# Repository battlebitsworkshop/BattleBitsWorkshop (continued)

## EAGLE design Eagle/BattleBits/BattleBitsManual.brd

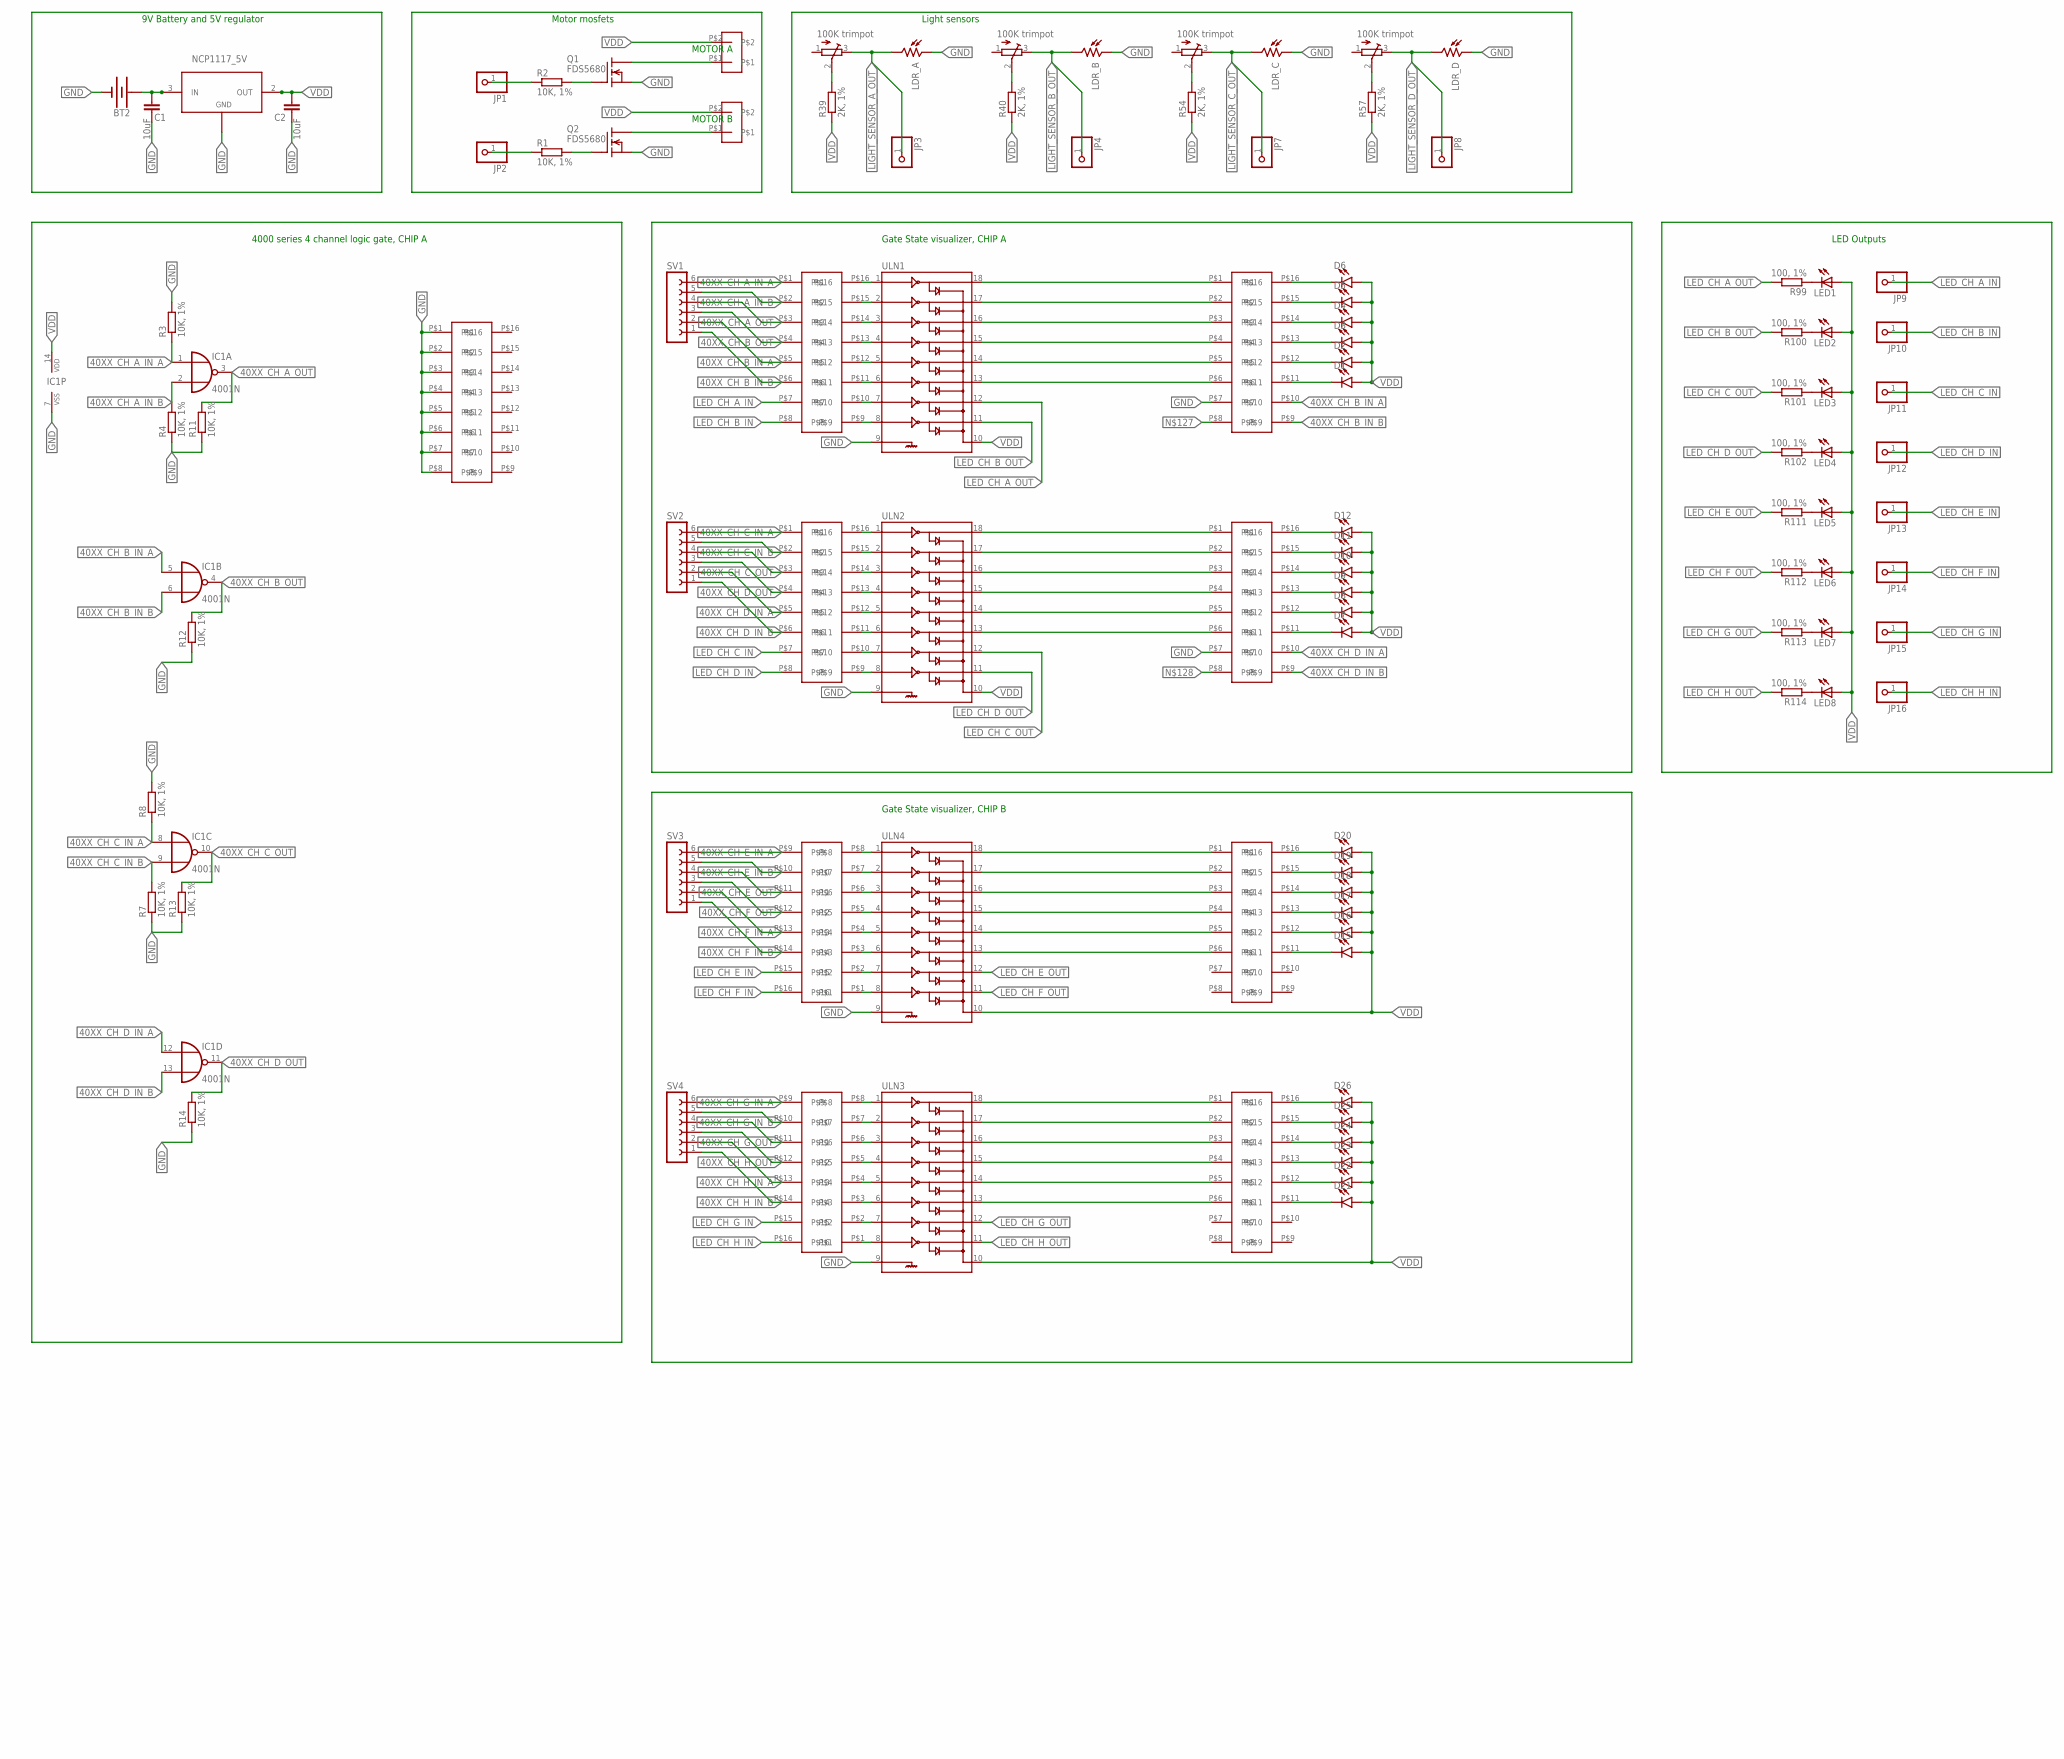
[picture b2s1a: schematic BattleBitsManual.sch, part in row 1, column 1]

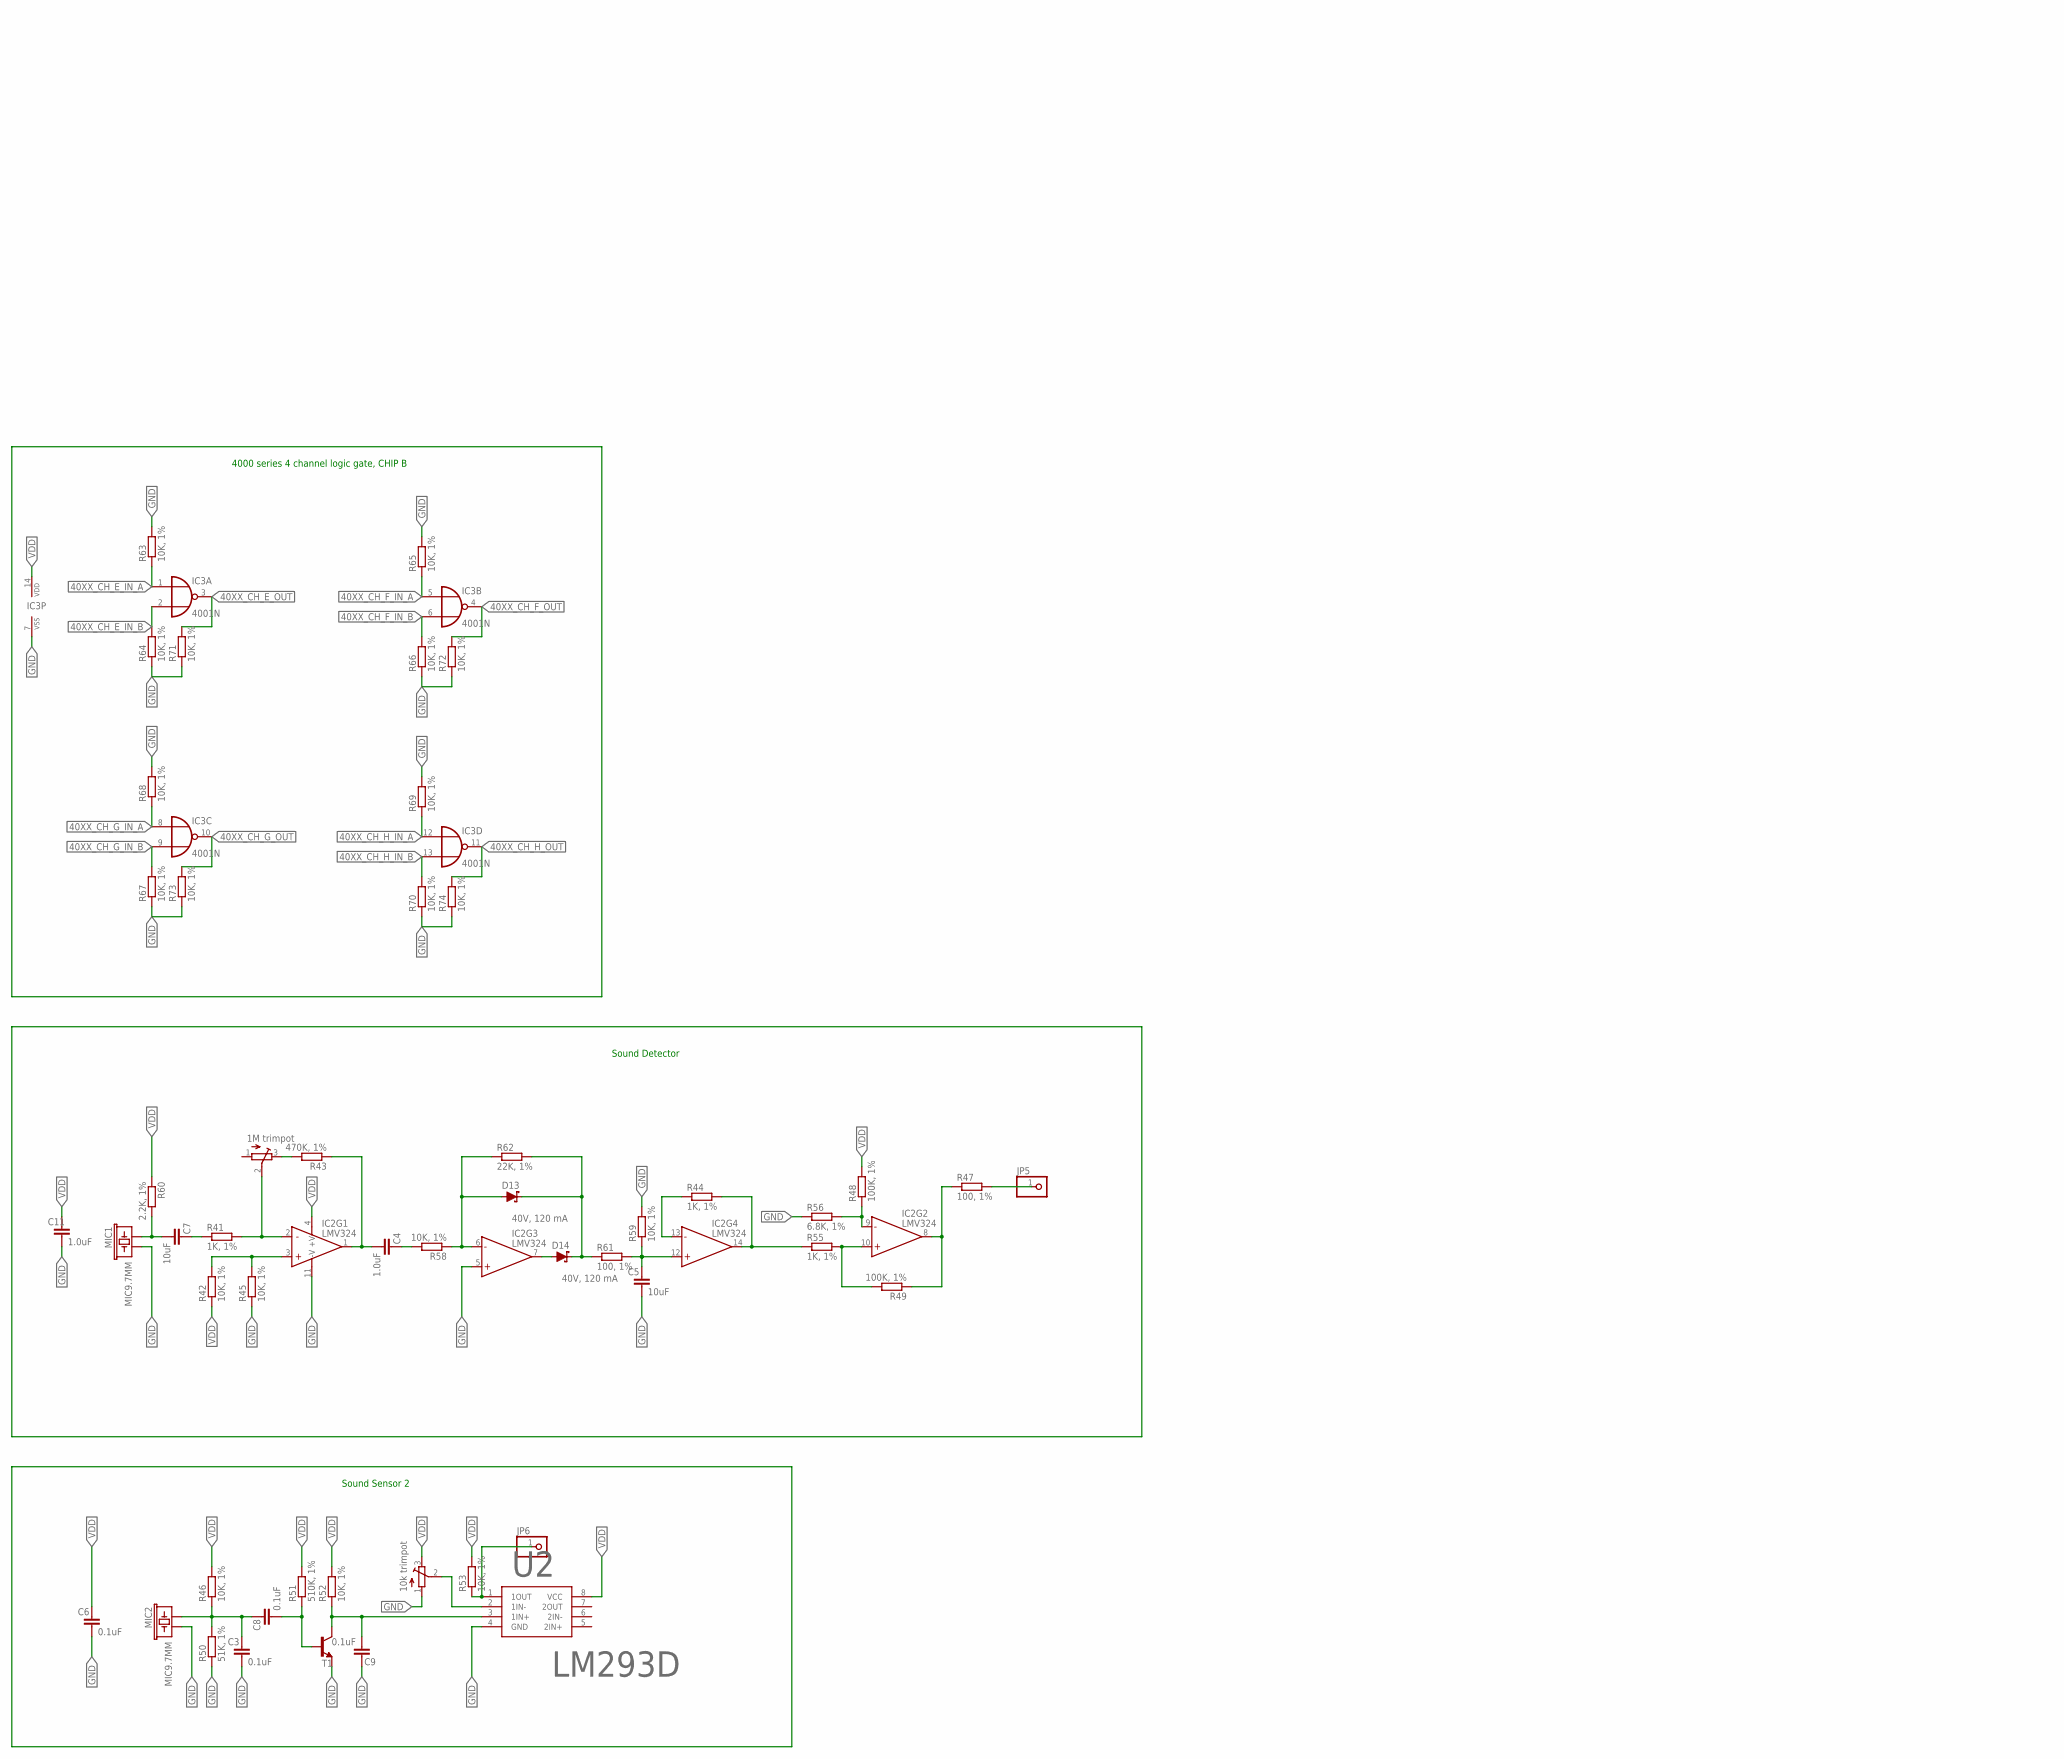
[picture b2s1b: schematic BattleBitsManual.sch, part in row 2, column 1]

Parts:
BT2: BATTERY-9V; BATTCON_9V
C1, C2, C5, C7: 10uF; C3216
C3, C6, C8, C9: 0.1uF; C3216
C4, C11: 1.0uF; C3216
D1, D2, D3, D4, D5, D6, D7, D8, D9, D10, D11, D12, D15, D16, D17, D18, D19, D20, D21, D22, D23, D24, D25, D26: LED1206; LED-1206
D13, D14: 40V, 120 mA; SOT23-3
IC1, IC3: 4001N; DIL14
IC2: LMV324; SO014
JP1, JP2, JP3, JP4, JP5, JP6, JP7, JP8, JP9, JP10, JP11, JP12, JP13, JP14, JP15, JP16: PINHD-1X1; 1X01
LDR_A: V1060_21; TO-5_V10
LDR_B: V1060_21; TO-5_V10
LDR_C: V1060_21; TO-5_V10
LDR_D: V1060_21; TO-5_V10
LED1, LED2, LED3, LED4, LED5, LED6, LED7, LED8: LED5MM
MIC1, MIC2: MIC9.7MM; MIC-9.7MM
Q1, Q2: FDS5680; SO-8
R1, R2, R3, R4, R7, R8, R11, R12, R13, R14, R42, R45, R46, R52, R53, R58, R59, R63, R64, R65, R66, R67, R68, R69, R70, R71, R72, R73, R74: 10K, 1%; R3216
R39, R40, R54, R57: 2K, 1%; R3216
R41, R44, R55: 1K, 1%; R3216
R43: 470K, 1%; R3216
R47, R61, R99, R100, R101, R102, R111, R112, R113, R114: 100, 1%; R3216
R48, R49: 100K, 1%; R3216
R50: 51K, 1%; R3216
R51: 510K, 1%; R3216
R56: 6.8K, 1%; R3216
R60: 2.2K, 1%; R3216
R62: 22K, 1%; R3216
SV1, SV2, SV3, SV4: FE06-1; FE06
T1: BC808-NPN-SOT23-BEC; SOT23-BEC
TM1, TM2, TM5, TM6: 100K trimpot; TC33X
TM3: 1M trimpot; TC33X
TM4: 10k trimpot; TC33X
U1: NCP1117_5V; SOT-223
U2: LM293D; 8-SOIC
U$1, U$2: MOTOR; GEARMOTOR
U$3, U$4, U$5, U$6, U$7, U$8, U$9, U$10, U$11: 8_RES_ISO_SOIC16
ULN1, ULN2, ULN3, ULN4: ULN2803SOICW; SO18L

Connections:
40XX_CH_A_IN_A: IC1.1 (I0), R3.1, SV1.6, U$9.P$1
40XX_CH_A_IN_B: IC1.2 (I1), R4.2, SV1.5, U$9.P$2
40XX_CH_A_OUT: IC1.3 (O), R11.2, SV1.4, U$9.P$3
40XX_CH_B_IN_A: IC1.5 (I0), SV1.2, U$3.P$10, U$9.P$5
40XX_CH_B_IN_B: IC1.6 (I1), SV1.1, U$3.P$9, U$9.P$6
40XX_CH_B_OUT: IC1.4 (O), R12.2, SV1.3, U$9.P$4
40XX_CH_C_IN_A: IC1.8 (I0), R8.1, SV2.6, U$4.P$1
40XX_CH_C_IN_B: IC1.9 (I1), R7.2, SV2.5, U$4.P$2
40XX_CH_C_OUT: IC1.10 (O), R13.2, SV2.4, U$4.P$3
40XX_CH_D_IN_A: IC1.12 (I0), SV2.2, U$4.P$5, U$7.P$10
40XX_CH_D_IN_B: IC1.13 (I1), SV2.1, U$4.P$6, U$7.P$9
40XX_CH_D_OUT: IC1.11 (O), R14.2, SV2.3, U$4.P$4
40XX_CH_E_IN_A: IC3.1 (I0), R63.1, SV3.6, U$5.P$9
40XX_CH_E_IN_B: IC3.2 (I1), R64.2, SV3.5, U$5.P$10
40XX_CH_E_OUT: IC3.3 (O), R71.2, SV3.4, U$5.P$11
40XX_CH_F_IN_A: IC3.5 (I0), R65.1, SV3.2, U$5.P$13
40XX_CH_F_IN_B: IC3.6 (I1), R66.2, SV3.1, U$5.P$14
40XX_CH_F_OUT: IC3.4 (O), R72.2, SV3.3, U$5.P$12
40XX_CH_G_IN_A: IC3.8 (I0), R68.1, SV4.6, U$6.P$9
40XX_CH_G_IN_B: IC3.9 (I1), R67.2, SV4.5, U$6.P$10
40XX_CH_G_OUT: IC3.10 (O), R73.2, SV4.4, U$6.P$11
40XX_CH_H_IN_A: IC3.12 (I0), R69.1, SV4.2, U$6.P$13
40XX_CH_H_IN_B: IC3.13 (I1), R70.2, SV4.1, U$6.P$14
40XX_CH_H_OUT: IC3.11 (O), R74.2, SV4.3, U$6.P$12
AMPENV: IC2.14 (OUT), R44.2, R55.1
GND: BT2.-, C1.1, C2.1, C3.2, C5.2, C6.2, C9.1, C11.2, IC1.7 (VSS), IC2.5 (+IN), IC2.11 (-V), IC3.7 (VSS), LDR_A.1, LDR_B.1, LDR_C.1, LDR_D.1, MIC1.2, MIC2.2, Q1.1 (S), Q1.2 (S), Q1.3 (S), Q2.1 (S), Q2.2 (S), Q2.3 (S), R3.2, R4.1, R7.1, R8.2, R11.1, R12.1, R13.1, R14.1, R45.1, R50.1, R56.1, R59.2, R63.2, R64.1, R65.2, R66.1, R67.1, R68.2, R69.2, R70.1, R71.1, R72.1, R73.1, R74.1, T1.E, TM4.1 (A), U1.1 (ADJ/GND), U2.4 (GND), U$3.P$7, U$7.P$7, U$8.P$1, U$8.P$2, U$8.P$3, U$8.P$4, U$8.P$5, U$8.P$6, U$8.P$7, U$8.P$8, ULN1.9, ULN2.9, ULN3.9, ULN4.9
LED_CH_A_IN: JP9.1, U$9.P$7
LED_CH_A_OUT: R99.2, ULN1.12
LED_CH_B_IN: JP10.1, U$9.P$8
LED_CH_B_OUT: R100.2, ULN1.11
LED_CH_C_IN: JP11.1, U$4.P$7
LED_CH_C_OUT: R101.2, ULN2.12
LED_CH_D_IN: JP12.1, U$4.P$8
LED_CH_D_OUT: R102.2, ULN2.11
LED_CH_E_IN: JP13.1, U$5.P$15
LED_CH_E_OUT: R111.2, ULN4.12
LED_CH_F_IN: JP14.1, U$5.P$16
LED_CH_F_OUT: R112.2, ULN4.11
LED_CH_G_IN: JP15.1, U$6.P$15
LED_CH_G_OUT: R113.2, ULN3.12
LED_CH_H_IN: JP16.1, U$6.P$16
LED_CH_H_OUT: R114.2, ULN3.11
LIGHT_SENSOR_A_OUT: JP3.1, LDR_A.2, TM1.3 (E)
LIGHT_SENSOR_B_OUT: JP4.1, LDR_B.2, TM2.3 (E)
LIGHT_SENSOR_C_OUT: JP7.1, LDR_C.2, TM5.3 (E)
LIGHT_SENSOR_D_OUT: JP8.1, LDR_D.2, TM6.3 (E)
MOTOR_A-: Q1.5 (D), Q1.6 (D), Q1.7 (D), Q1.8 (D), U$1.P$1
MOTOR_B-: Q2.5 (D), Q2.6 (D), Q2.7 (D), Q2.8 (D), U$2.P$1
N$: C4.2, IC2.1 (OUT), R43.1
unnamed: U$9.P$16, ULN1.1
unnamed: Q1.4 (G), R2.2
unnamed: Q2.4 (G), R1.2
unnamed: U$9.P$15, ULN1.2
unnamed: U$9.P$14, ULN1.3
unnamed: U$9.P$13, ULN1.4
unnamed: U$9.P$12, ULN1.5
unnamed: U$9.P$11, ULN1.6
unnamed: U$4.P$16, ULN2.1
unnamed: U$4.P$15, ULN2.2
unnamed: U$4.P$14, ULN2.3
unnamed: U$4.P$13, ULN2.4
unnamed: U$4.P$12, ULN2.5
unnamed: U$4.P$11, ULN2.6
unnamed: U$3.P$1, ULN1.18
unnamed: D6.C, U$3.P$16
unnamed: U$3.P$2, ULN1.17
unnamed: D5.C, U$3.P$15
unnamed: U$3.P$3, ULN1.16
unnamed: D4.C, U$3.P$14
unnamed: U$3.P$4, ULN1.15
unnamed: D3.C, U$3.P$13
unnamed: U$3.P$5, ULN1.14
unnamed: D2.C, U$3.P$12
unnamed: U$3.P$6, ULN1.13
unnamed: D1.C, U$3.P$11
unnamed: U$7.P$1, ULN2.18
unnamed: U$7.P$3, ULN2.16
unnamed: U$7.P$4, ULN2.15
unnamed: U$7.P$5, ULN2.14
unnamed: U$7.P$6, ULN2.13
unnamed: D12.C, U$7.P$16
unnamed: D11.C, U$7.P$15
unnamed: U$7.P$2, ULN2.17
unnamed: D10.C, U$7.P$14
unnamed: D9.C, U$7.P$13
unnamed: D8.C, U$7.P$12
unnamed: D7.C, U$7.P$11
unnamed: R39.2, TM1.2 (S)
unnamed: R40.2, TM2.2 (S)
unnamed: C7.2, MIC1.1, R60.2
unnamed: IC2.3 (+IN), R42.2, R45.2
unnamed: IC2.2 (-IN), R41.2, TM3.2 (S)
unnamed: C7.1, R41.1
unnamed: C4.1, R58.2
unnamed: D13.1 (A), IC2.6 (-IN), R58.1, R62.1
unnamed: D14.1 (A), IC2.7 (OUT)
unnamed: D13.3 (C), D14.3 (C), R61.1, R62.2
unnamed: C5.1, IC2.12 (+IN), R59.1, R61.2
unnamed: IC2.13 (-IN), R44.1
unnamed: IC2.9 (-IN), R48.1, R56.2
unnamed: IC2.10 (+IN), R49.2, R55.2
unnamed: IC2.8 (OUT), R47.1, R49.1
unnamed: R43.2, TM3.3 (E)
unnamed: C3.1, C8.1, MIC2.1, R46.1, R50.2
unnamed: C8.2, R51.1, T1.B
unnamed: C9.2, R52.1, T1.C, U2.3 (1IN+)
unnamed: TM4.2 (S), U2.2 (1IN-)
unnamed: JP6.1, R53.1, U2.1 (1OUT)
unnamed: JP1.1, R2.1
unnamed: JP2.1, R1.1
unnamed: JP5.1, R47.2
unnamed: R54.2, TM5.2 (S)
unnamed: R57.2, TM6.2 (S)
unnamed: U$5.P$8, ULN4.1
unnamed: U$5.P$7, ULN4.2
unnamed: U$5.P$6, ULN4.3
unnamed: U$5.P$5, ULN4.4
unnamed: U$5.P$4, ULN4.5
unnamed: U$5.P$3, ULN4.6
unnamed: U$6.P$8, ULN3.1
unnamed: U$6.P$7, ULN3.2
unnamed: U$6.P$6, ULN3.3
unnamed: U$6.P$5, ULN3.4
unnamed: U$6.P$4, ULN3.5
unnamed: U$6.P$3, ULN3.6
unnamed: D20.C, U$10.P$16
unnamed: D19.C, U$10.P$15
unnamed: D18.C, U$10.P$14
unnamed: D17.C, U$10.P$13
unnamed: D16.C, U$10.P$12
unnamed: D15.C, U$10.P$11
unnamed: D26.C, U$11.P$16
unnamed: D25.C, U$11.P$15
unnamed: D24.C, U$11.P$14
unnamed: D23.C, U$11.P$13
unnamed: D22.C, U$11.P$12
unnamed: D21.C, U$11.P$11
unnamed: U$10.P$1, ULN4.18
unnamed: U$10.P$2, ULN4.17
unnamed: U$10.P$3, ULN4.16
unnamed: U$10.P$4, ULN4.15
unnamed: U$10.P$5, ULN4.14
unnamed: U$10.P$6, ULN4.13
unnamed: U$11.P$1, ULN3.18
unnamed: U$11.P$2, ULN3.17
unnamed: U$11.P$3, ULN3.16
unnamed: U$11.P$4, ULN3.15
unnamed: U$11.P$5, ULN3.14
unnamed: U$11.P$6, ULN3.13
unnamed: LED1.K (C), R99.1
unnamed: LED2.K (C), R100.1
unnamed: LED3.K (C), R101.1
unnamed: LED4.K (C), R102.1
unnamed: U$9.P$10, ULN1.7
unnamed: U$9.P$9, ULN1.8
unnamed: U$4.P$10, ULN2.7
unnamed: U$4.P$9, ULN2.8
unnamed: U$5.P$2, ULN4.7
unnamed: U$5.P$1, ULN4.8
unnamed: U$6.P$2, ULN3.7
unnamed: U$6.P$1, ULN3.8
unnamed: LED5.K (C), R111.1
unnamed: LED6.K (C), R112.1
unnamed: LED7.K (C), R113.1
unnamed: LED8.K (C), R114.1
VBAT: BT2.+, C1.2, U1.3 (IN)
VDD: C2.2, C6.1, C11.1, D1.A, D2.A, D3.A, D4.A, D5.A, D6.A, D7.A, D8.A, D9.A, D10.A, D11.A, D12.A, D15.A, D16.A, D17.A, D18.A, D19.A, D20.A, D21.A, D22.A, D23.A, D24.A, D25.A, D26.A, IC1.14 (VDD), IC2.4 (+V), IC3.14 (VDD), LED1.A, LED2.A, LED3.A, LED4.A, LED5.A, LED6.A, LED7.A, LED8.A, R39.1, R40.1, R42.1, R46.2, R48.2, R51.2, R52.2, R53.2, R54.1, R57.1, R60.1, TM4.3 (E), U1.2 (OUT), U1.4, U2.8 (VCC), U$1.P$2, U$2.P$2, ULN1.10, ULN2.10, ULN3.10, ULN4.10

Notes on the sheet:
4000 series 4 channel logic gate, CHIP A
9V Battery and 5V regulator
Motor mosfets
MOTOR A
MOTOR B
Gate State visualizer, CHIP A
Light sensors
Sound Detector
Sound Sensor 2
4000 series 4 channel logic gate, CHIP B
Gate State visualizer, CHIP B
LED Outputs

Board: 2 copper layers, 154 parts (1 on the bottom side), 167 nets, no tracks yet.

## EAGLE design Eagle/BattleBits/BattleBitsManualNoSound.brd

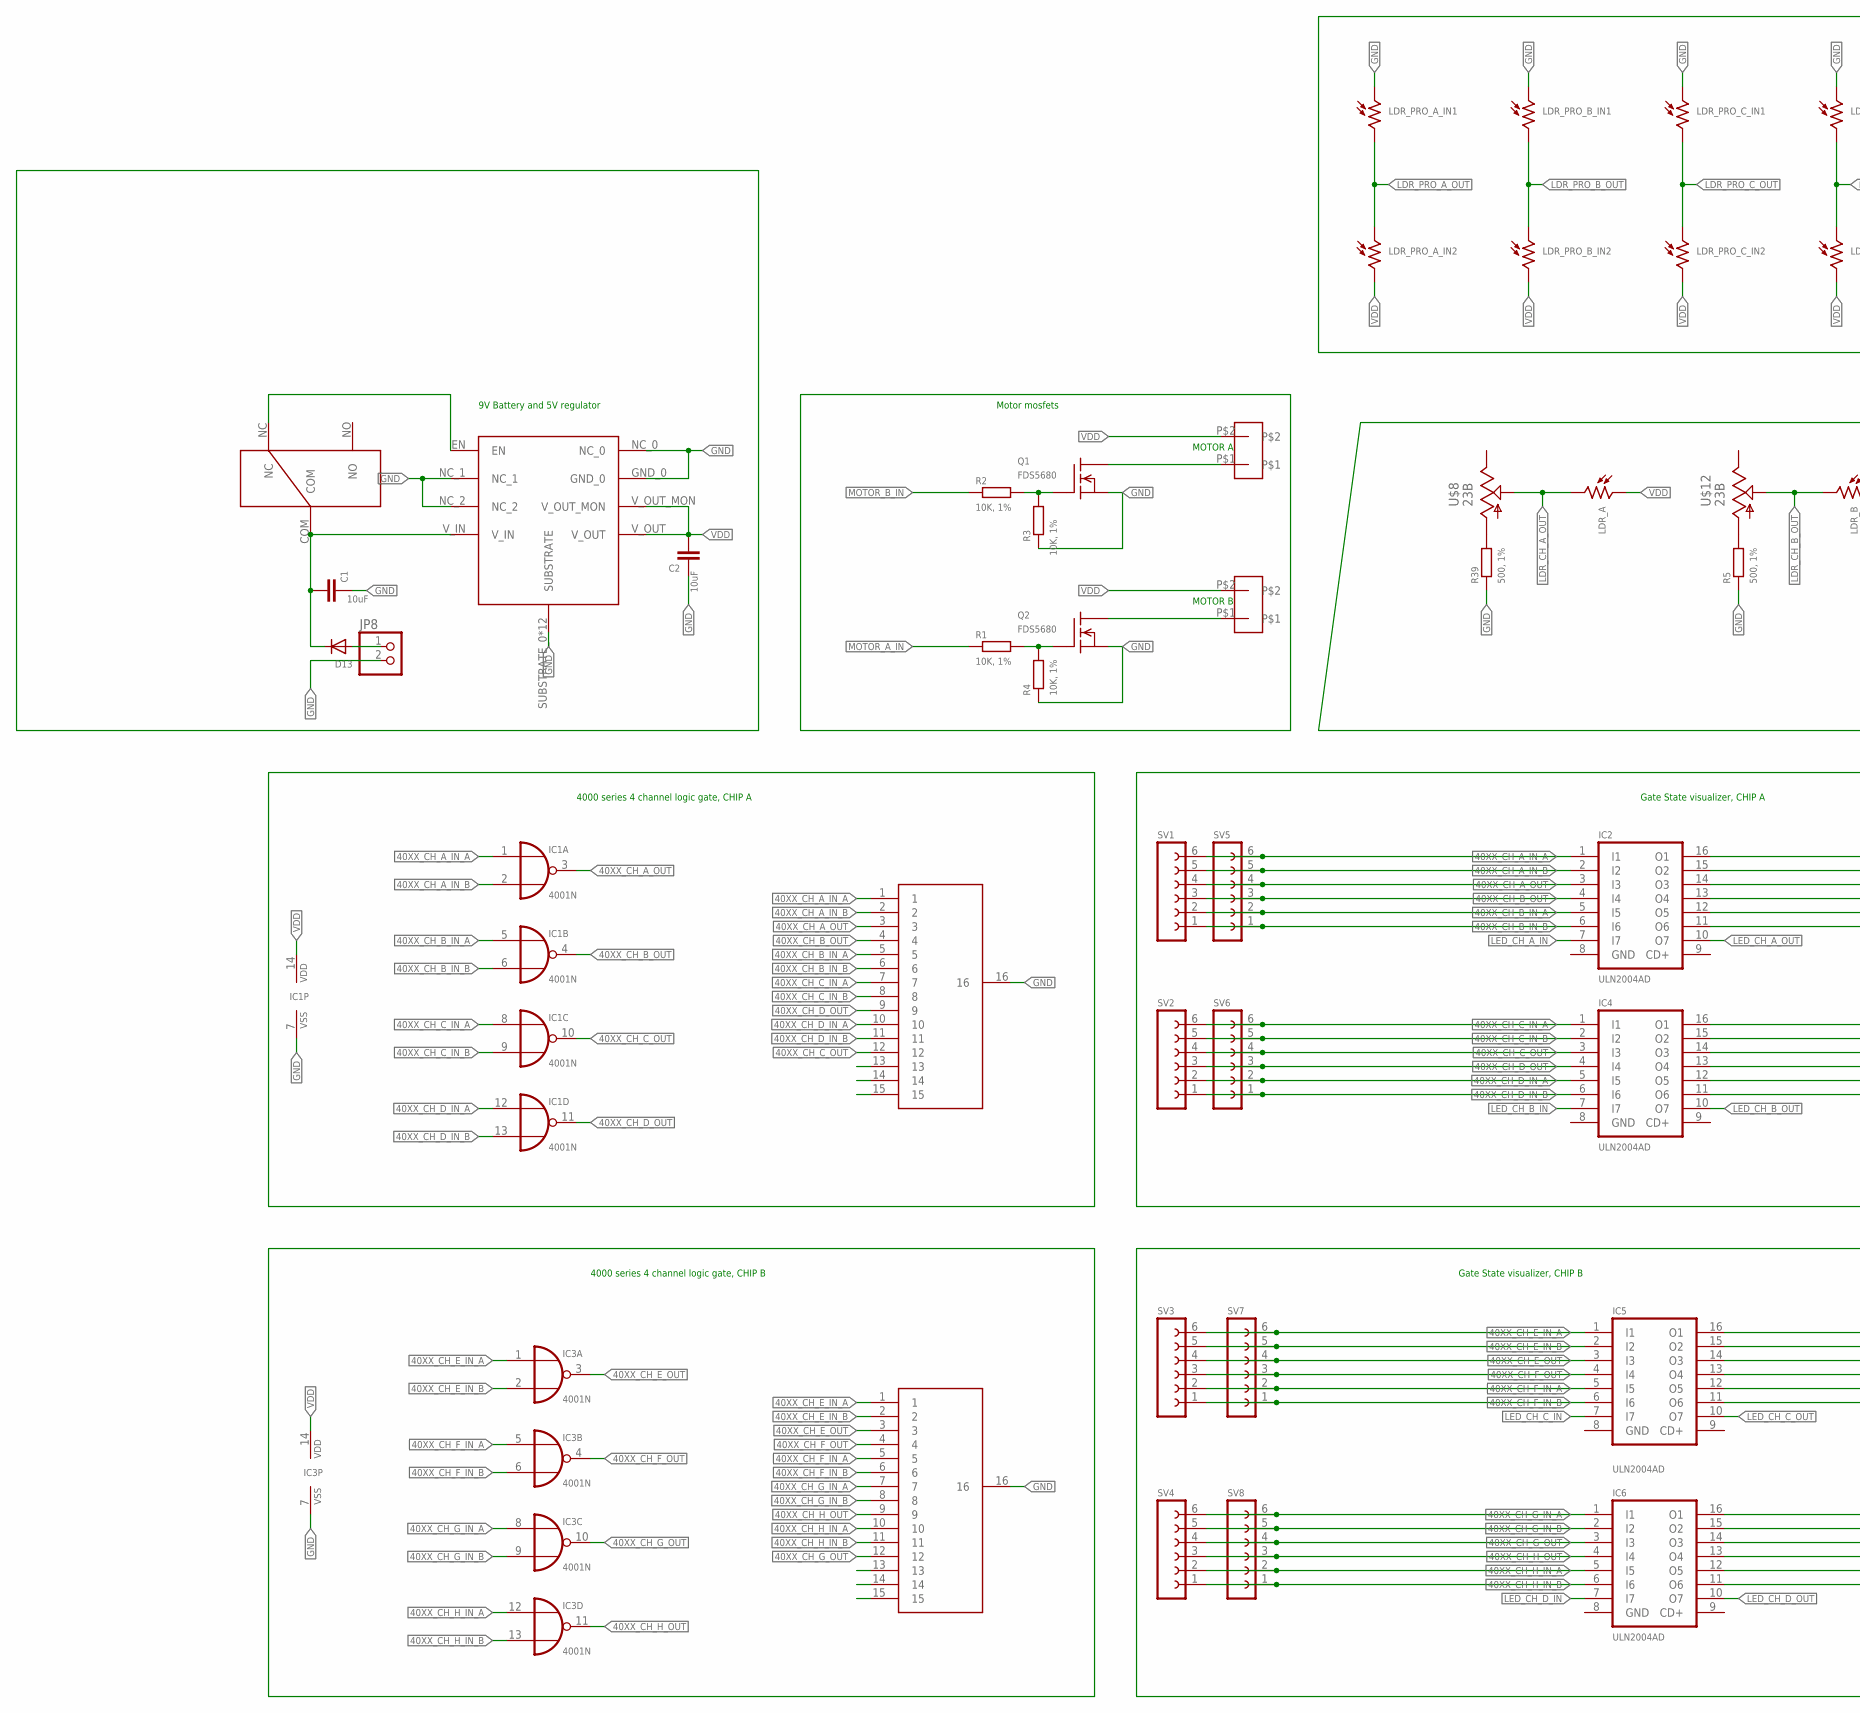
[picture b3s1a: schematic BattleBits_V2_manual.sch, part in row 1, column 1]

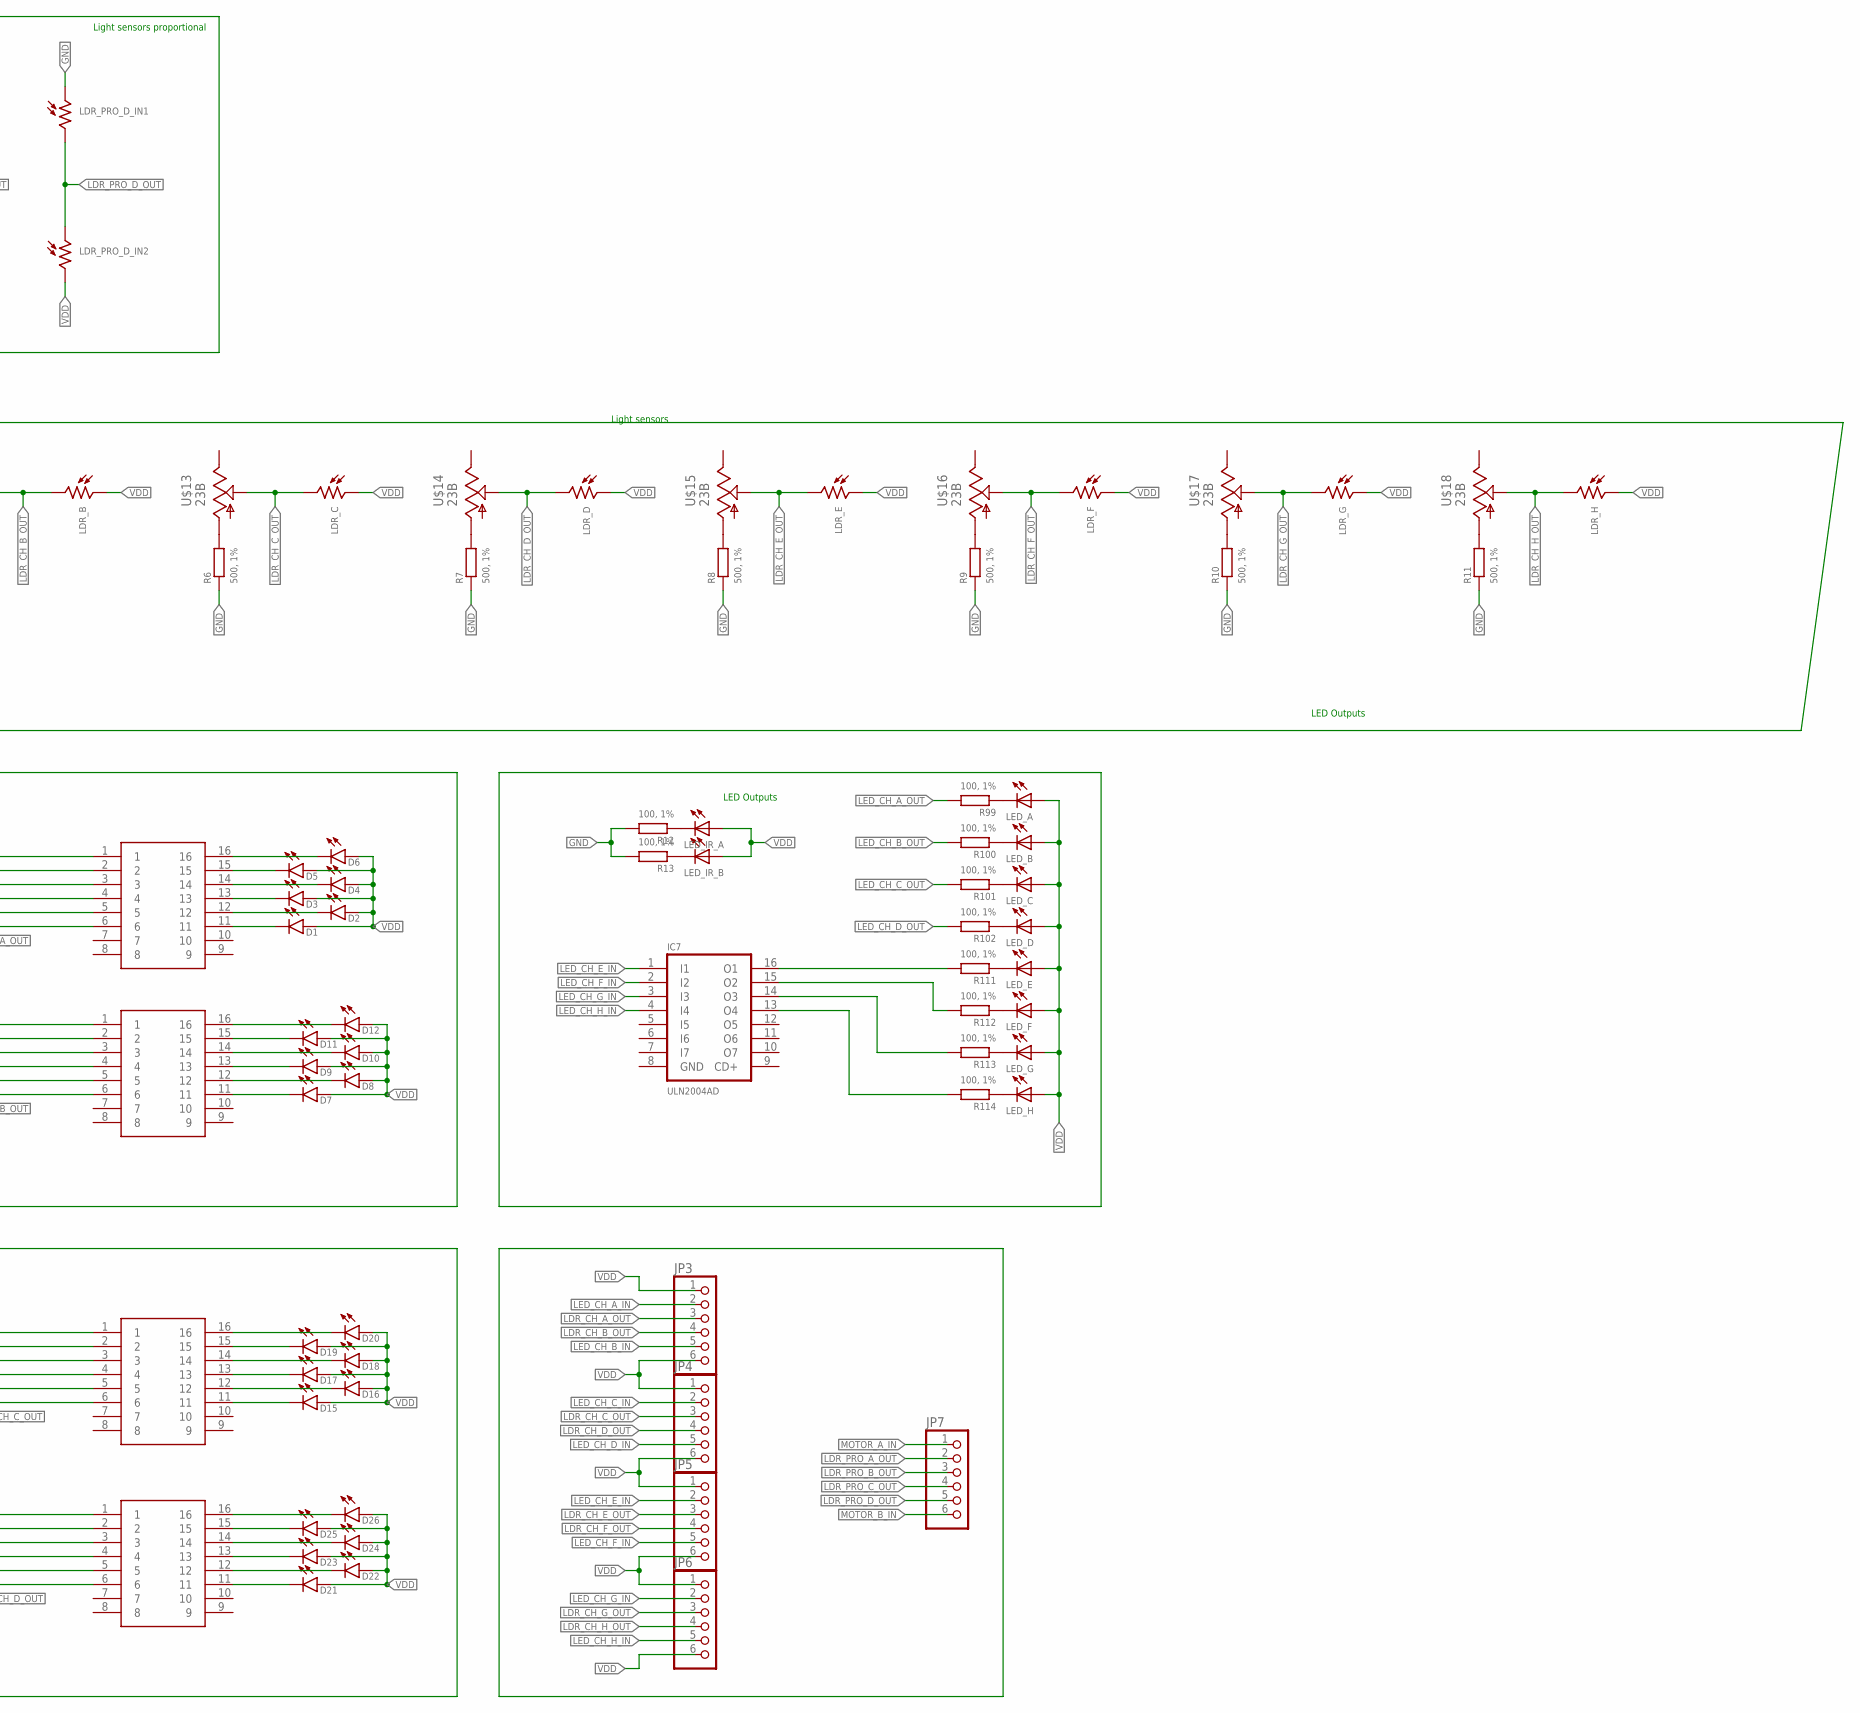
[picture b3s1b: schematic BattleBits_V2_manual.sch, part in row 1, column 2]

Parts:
C1, C2: 10uF; C3216
D1, D2, D3, D4, D5, D6, D7, D8, D9, D10, D11, D12, D15, D16, D17, D18, D19, D20, D21, D22, D23, D24, D25, D26: LED1206; LED-1206
D13: DIODESMA; SMADIODE
IC1, IC3: 4001N; DIL14
IC2, IC4, IC5, IC6, IC7: ULN2004AD; SO16
JP3, JP4, JP5, JP6, JP7: PINHD-1X6; 1X06
JP8: PINHD-1X2; 1X02
LDR_A: V1060_21; TO-5_V10
LDR_B: V1060_21; TO-5_V10
LDR_C: V1060_21; TO-5_V10
LDR_D: V1060_21; TO-5_V10
LDR_E: V1060_21; TO-5_V10
LDR_F: V1060_21; TO-5_V10
LDR_G: V1060_21; TO-5_V10
LDR_H: V1060_21; TO-5_V10
LDR_PRO_A_IN1, LDR_PRO_A_IN2: V1060_21; TO-5_V10
LDR_PRO_B_IN1, LDR_PRO_B_IN2: V1060_21; TO-5_V10
LDR_PRO_C_IN1, LDR_PRO_C_IN2: V1060_21; TO-5_V10
LDR_PRO_D_IN1, LDR_PRO_D_IN2: V1060_21; TO-5_V10
LED_A: LED5MM
LED_B: LED5MM
LED_C: LED5MM
LED_D: LED5MM
LED_E: LED5MM
LED_F: LED5MM
LED_G: LED5MM
LED_H: LED5MM
LED_IR_A: LED5MM
LED_IR_B: LED5MM
Q1, Q2: FDS5680; SO-8
R1, R2, R3, R4: 10K, 1%; R3216
R5, R6, R7, R8, R9, R10, R11, R39: 500, 1%; R3216
R12, R13, R99, R100, R101, R102, R111, R112, R113, R114: 100, 1%; R3216
SV1, SV2, SV3, SV4, SV5, SV6, SV7, SV8: FE06-1; FE06
U$1, U$2: MOTOR; GEARMOTOR
U$3, U$11: 15_RES_BUS_SOIC16; SO16
U$4: ROHM_LDO; HTSOP-J8
U$5, U$6, U$9, U$10: 8_RES_ISO_SOIC-16; SO16
U$7: SLIDE_SWITCH
U$8, U$12, U$13, U$14, U$15, U$16, U$17, U$18: 23B; 23B-GULL_WING

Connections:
40XX_CH_A_IN_A: IC1.1 (I0), IC2.1 (I1), SV1.6, SV5.6, U$11.1
40XX_CH_A_IN_B: IC1.2 (I1), IC2.2 (I2), SV1.5, SV5.5, U$11.2
40XX_CH_A_OUT: IC1.3 (O), IC2.3 (I3), SV1.4, SV5.4, U$11.3
40XX_CH_B_IN_A: IC1.5 (I0), IC2.5 (I5), SV1.2, SV5.2, U$11.5
40XX_CH_B_IN_B: IC1.6 (I1), IC2.6 (I6), SV1.1, SV5.1, U$11.6
40XX_CH_B_OUT: IC1.4 (O), IC2.4 (I4), SV1.3, SV5.3, U$11.4
40XX_CH_C_IN_A: IC1.8 (I0), IC4.1 (I1), SV2.6, SV6.6, U$11.7
40XX_CH_C_IN_B: IC1.9 (I1), IC4.2 (I2), SV2.5, SV6.5, U$11.8
40XX_CH_C_OUT: IC1.10 (O), IC4.3 (I3), SV2.4, SV6.4, U$11.12
40XX_CH_D_IN_A: IC1.12 (I0), IC4.5 (I5), SV2.2, SV6.2, U$11.10
40XX_CH_D_IN_B: IC1.13 (I1), IC4.6 (I6), SV2.1, SV6.1, U$11.11
40XX_CH_D_OUT: IC1.11 (O), IC4.4 (I4), SV2.3, SV6.3, U$11.9
40XX_CH_E_IN_A: IC3.1 (I0), IC5.1 (I1), SV3.6, SV7.6, U$3.1
40XX_CH_E_IN_B: IC3.2 (I1), IC5.2 (I2), SV3.5, SV7.5, U$3.2
40XX_CH_E_OUT: IC3.3 (O), IC5.3 (I3), SV3.4, SV7.4, U$3.3
40XX_CH_F_IN_A: IC3.5 (I0), IC5.5 (I5), SV3.2, SV7.2, U$3.5
40XX_CH_F_IN_B: IC3.6 (I1), IC5.6 (I6), SV3.1, SV7.1, U$3.6
40XX_CH_F_OUT: IC3.4 (O), IC5.4 (I4), SV3.3, SV7.3, U$3.4
40XX_CH_G_IN_A: IC3.8 (I0), IC6.1 (I1), SV4.6, SV8.6, U$3.7
40XX_CH_G_IN_B: IC3.9 (I1), IC6.2 (I2), SV4.5, SV8.5, U$3.8
40XX_CH_G_OUT: IC3.10 (O), IC6.3 (I3), SV4.4, SV8.4, U$3.12
40XX_CH_H_IN_A: IC3.12 (I0), IC6.5 (I5), SV4.2, SV8.2, U$3.10
40XX_CH_H_IN_B: IC3.13 (I1), IC6.6 (I6), SV4.1, SV8.1, U$3.11
40XX_CH_H_OUT: IC3.11 (O), IC6.4 (I4), SV4.3, SV8.3, U$3.9
GND: C1.1, C2.1, IC1.7 (VSS), IC2.8 (GND), IC3.7 (VSS), IC4.8 (GND), IC5.8 (GND), IC6.8 (GND), IC7.8 (GND), JP8.2, LDR_PRO_A_IN1.1, LDR_PRO_B_IN1.1, LDR_PRO_C_IN1.1, LDR_PRO_D_IN1.1, Q1.1 (S), Q1.2 (S), Q1.3 (S), Q2.1 (S), Q2.2 (S), Q2.3 (S), R3.1, R4.1, R5.1, R6.1, R7.1, R8.1, R9.1, R10.1, R11.1, R12.2, R13.2, R39.1, U$3.16, U$4.GND_0, U$4.NC_0, U$4.NC_1, U$4.NC_2, U$4.SUBSTRATE_0 (SUBSTRATE), U$4.SUBSTRATE_1 (SUBSTRATE), U$4.SUBSTRATE_2 (SUBSTRATE), U$4.SUBSTRATE_3 (SUBSTRATE), U$4.SUBSTRATE_4 (SUBSTRATE), U$4.SUBSTRATE_5 (SUBSTRATE), U$4.SUBSTRATE_6 (SUBSTRATE), U$4.SUBSTRATE_7 (SUBSTRATE), U$4.SUBSTRATE_8 (SUBSTRATE), U$4.SUBSTRATE_9 (SUBSTRATE), U$4.SUBSTRATE_10 (SUBSTRATE), U$4.SUBSTRATE_11 (SUBSTRATE), U$11.16
LDR_CH_A_OUT: JP3.3, LDR_A.2, U$8.2
LDR_CH_B_OUT: JP3.4, LDR_B.2, U$12.2
LDR_CH_C_OUT: JP4.3, LDR_C.2, U$13.2
LDR_CH_D_OUT: JP4.4, LDR_D.2, U$14.2
LDR_CH_E_OUT: JP5.3, LDR_E.2, U$15.2
LDR_CH_F_OUT: JP5.4, LDR_F.2, U$16.2
LDR_CH_G_OUT: JP6.3, LDR_G.2, U$17.2
LDR_CH_H_OUT: JP6.4, LDR_H.2, U$18.2
LDR_PRO_A_OUT: JP7.2, LDR_PRO_A_IN1.2, LDR_PRO_A_IN2.1
LDR_PRO_B_OUT: JP7.3, LDR_PRO_B_IN1.2, LDR_PRO_B_IN2.1
LDR_PRO_C_OUT: JP7.4, LDR_PRO_C_IN1.2, LDR_PRO_C_IN2.1
LDR_PRO_D_OUT: JP7.5, LDR_PRO_D_IN1.2, LDR_PRO_D_IN2.1
LED_CH_A_IN: IC2.7 (I7), JP3.2
LED_CH_A_OUT: IC2.10 (O7), R99.2
LED_CH_B_IN: IC4.7 (I7), JP3.5
LED_CH_B_OUT: IC4.10 (O7), R100.2
LED_CH_C_IN: IC5.7 (I7), JP4.2
LED_CH_C_OUT: IC5.10 (O7), R101.2
LED_CH_D_IN: IC6.7 (I7), JP4.5
LED_CH_D_OUT: IC6.10 (O7), R102.2
LED_CH_E_IN: IC7.1 (I1), JP5.2
LED_CH_F_IN: IC7.2 (I2), JP5.5
LED_CH_G_IN: IC7.3 (I3), JP6.2
LED_CH_H_IN: IC7.4 (I4), JP6.5
MOTOR_A-: Q1.5 (D), Q1.6 (D), Q1.7 (D), Q1.8 (D), U$1.P$1
MOTOR_A_IN: JP7.1, R1.1
MOTOR_B-: Q2.5 (D), Q2.6 (D), Q2.7 (D), Q2.8 (D), U$2.P$1
MOTOR_B_IN: JP7.6, R2.1
unnamed: IC2.16 (O1), U$5.1
unnamed: Q1.4 (G), R2.2, R3.2
unnamed: Q2.4 (G), R1.2, R4.2
unnamed: IC2.15 (O2), U$5.2
unnamed: IC2.14 (O3), U$5.3
unnamed: IC2.13 (O4), U$5.4
unnamed: IC2.12 (O5), U$5.5
unnamed: IC2.11 (O6), U$5.6
unnamed: IC6.16 (O1), U$10.1
unnamed: IC4.16 (O1), U$6.1
unnamed: IC4.15 (O2), U$6.2
unnamed: IC4.14 (O3), U$6.3
unnamed: IC4.13 (O4), U$6.4
unnamed: IC4.12 (O5), U$6.5
unnamed: IC4.11 (O6), U$6.6
unnamed: D6.C, U$5.16
unnamed: IC6.14 (O3), U$10.3
unnamed: D5.C, U$5.15
unnamed: IC5.16 (O1), U$9.1
unnamed: D4.C, U$5.14
unnamed: IC5.15 (O2), U$9.2
unnamed: D3.C, U$5.13
unnamed: IC5.14 (O3), U$9.3
unnamed: D2.C, U$5.12
unnamed: IC5.13 (O4), U$9.4
unnamed: D1.C, U$5.11
unnamed: IC5.12 (O5), U$9.5
unnamed: IC5.11 (O6), U$9.6
unnamed: IC6.15 (O2), U$10.2
unnamed: IC6.13 (O4), U$10.4
unnamed: IC6.12 (O5), U$10.5
unnamed: D12.C, U$6.16
unnamed: D11.C, U$6.15
unnamed: IC6.11 (O6), U$10.6
unnamed: D10.C, U$6.14
unnamed: D9.C, U$6.13
unnamed: D8.C, U$6.12
unnamed: D7.C, U$6.11
unnamed: R39.2, U$8.1
unnamed: R5.2, U$12.1
unnamed: IC7.16 (O1), R111.2
unnamed: IC7.15 (O2), R112.2
unnamed: IC7.14 (O3), R113.2
unnamed: IC7.13 (O4), R114.2
unnamed: R6.2, U$13.1
unnamed: R7.2, U$14.1
unnamed: R8.2, U$15.1
unnamed: R9.2, U$16.1
unnamed: R10.2, U$17.1
unnamed: R11.2, U$18.1
unnamed: D13.A, JP8.1
unnamed: U$4.EN, U$7.NC
unnamed: LED_IR_A.K (C), R12.1
unnamed: LED_IR_B.K (C), R13.1
unnamed: D20.C, U$9.16
unnamed: D19.C, U$9.15
unnamed: D18.C, U$9.14
unnamed: D17.C, U$9.13
unnamed: D16.C, U$9.12
unnamed: D15.C, U$9.11
unnamed: D26.C, U$10.16
unnamed: D25.C, U$10.15
unnamed: D24.C, U$10.14
unnamed: D23.C, U$10.13
unnamed: D22.C, U$10.12
unnamed: D21.C, U$10.11
unnamed: LED_A.K (C), R99.1
unnamed: LED_B.K (C), R100.1
unnamed: LED_C.K (C), R101.1
unnamed: LED_D.K (C), R102.1
unnamed: LED_E.K (C), R111.1
unnamed: LED_F.K (C), R112.1
unnamed: LED_G.K (C), R113.1
unnamed: LED_H.K (C), R114.1
VBAT: C1.2, D13.C, U$4.V_IN, U$7.COM
VDD: C2.2, D1.A, D2.A, D3.A, D4.A, D5.A, D6.A, D7.A, D8.A, D9.A, D10.A, D11.A, D12.A, D15.A, D16.A, D17.A, D18.A, D19.A, D20.A, D21.A, D22.A, D23.A, D24.A, D25.A, D26.A, IC1.14 (VDD), IC3.14 (VDD), JP3.1, JP3.6, JP4.1, JP4.6, JP5.1, JP5.6, JP6.1, JP6.6, LDR_A.1, LDR_B.1, LDR_C.1, LDR_D.1, LDR_E.1, LDR_F.1, LDR_G.1, LDR_H.1, LDR_PRO_A_IN2.2, LDR_PRO_B_IN2.2, LDR_PRO_C_IN2.2, LDR_PRO_D_IN2.2, LED_A.A, LED_B.A, LED_C.A, LED_D.A, LED_E.A, LED_F.A, LED_G.A, LED_H.A, LED_IR_A.A, LED_IR_B.A, U$1.P$2, U$2.P$2, U$4.V_OUT, U$4.V_OUT_MON

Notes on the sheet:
4000 series 4 channel logic gate, CHIP A
9V Battery and 5V regulator
Motor mosfets
MOTOR A
MOTOR B
Gate State visualizer, CHIP A
Light sensors
4000 series 4 channel logic gate, CHIP B
Gate State visualizer, CHIP B
LED Outputs
Light sensors proportional

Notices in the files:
parts and their libraries:
SparkFun-IC-Special-Function: Licensing: Creative Commons ShareAlike 4.0 International - https://creativecommons.org/licenses/by-sa/4.0
SparkFun-Sensors: Licensing: CC v3.0 Share-Alike You are welcome to use this library for commercial purposes.
